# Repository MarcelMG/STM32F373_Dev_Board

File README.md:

# STM32F373_Dev_Board
a development board for the STM32F373 microcontroller with USB and separate analog power supply

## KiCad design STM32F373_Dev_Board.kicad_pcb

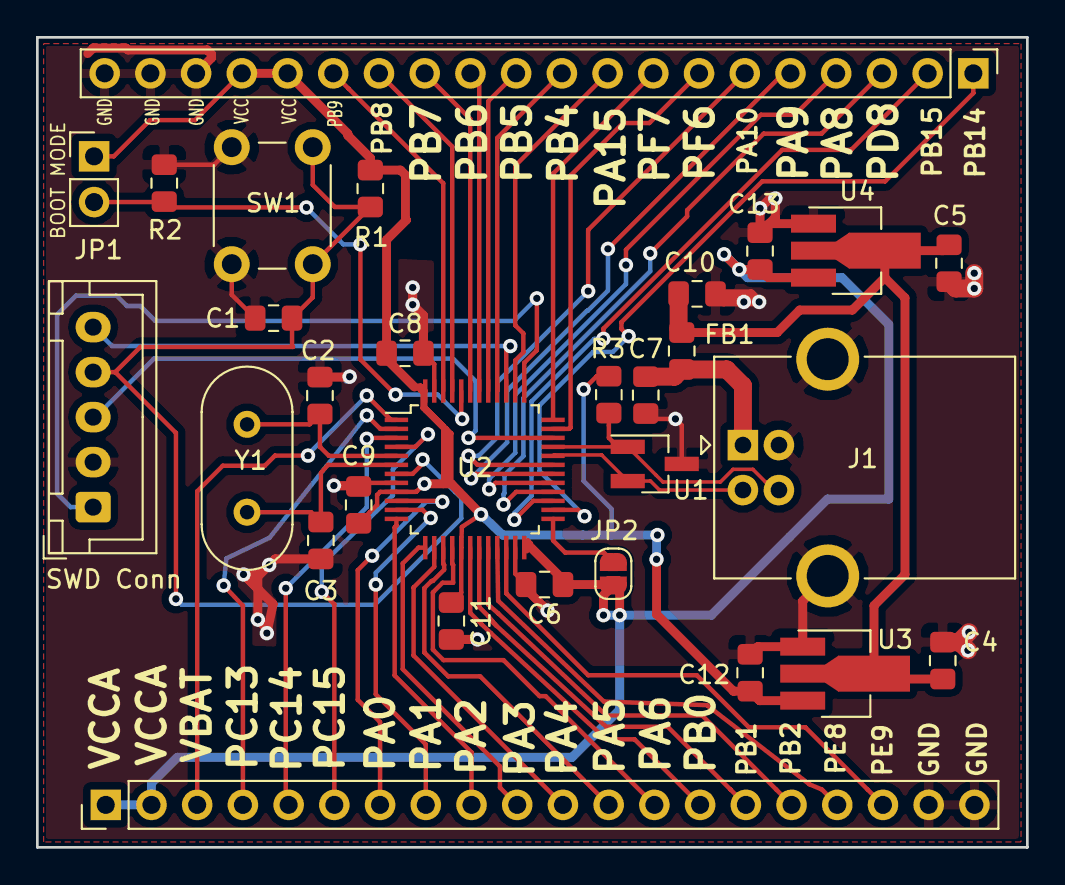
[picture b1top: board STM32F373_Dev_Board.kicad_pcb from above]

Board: 2 copper layers, 55.0 x 45.0 mm, 29 parts (0 on the bottom side), 46 nets.

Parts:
C1, C10: 100n; C_0805_2012Metric_Pad1.15x1.40mm_HandSolder
C2, C3: 27pF; C_0805_2012Metric_Pad1.15x1.40mm_HandSolder
C4, C5: 4.7µ; C_0805_2012Metric_Pad1.15x1.40mm_HandSolder
C6, C7, C8, C9, C11: 10n; C_0805_2012Metric_Pad1.15x1.40mm_HandSolder
C12, C13: 1µ; C_0805_2012Metric_Pad1.15x1.40mm_HandSolder
FB1: BLM21BB; L_0805_2012Metric_Pad1.15x1.40mm_HandSolder
J1: USB_B_female; USB_B_OST_USB-B1HSxx_Horizontal
J3, J4: Conn_01x20; PinHeader_1x20_P2.54mm_Vertical
JP1: Jumper; PinHeader_1x02_P2.54mm_Vertical
JP2: Jumper; SolderJumper-2_P1.3mm_Open_RoundedPad1.0x1.5mm
R1, R2: 10k; R_0805_2012Metric_Pad1.15x1.40mm_HandSolder
R3: 1.5k; R_0805_2012Metric_Pad1.15x1.40mm_HandSolder
SW1: SW_Push; SW_PUSH_6mm_H5mm
SWD Conn: SWD ST-Link Connector; JST_XH_B05B-XH-A_1x05_P2.50mm_Vertical
U1: TPD2E009; SOT-23_Handsoldering
U2: STM32F373CCTx; LQFP-48_7x7mm_P0.5mm
U3, U4: AP7215; SOT-89-3_Handsoldering
Y1: 8 MHz; Crystal_HC49-U_Vertical

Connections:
+3.3VA: C6.1, C13.1, J3.1, J3.2, JP2.2, U2.24, U4.3
+3V3: C8.1, C9.1, C11.1, C12.1, J4.16, J4.17, JP1.1, R1.2, R3.1, U2.9, U2.17, U2.48, U3.3
+5V: C4.1, C5.1, C10.2, FB1.1, U3.2, U4.2
BOOT0: JP1.2, R2.2, U2.44
GND: C1.1, C2.2, C3.2, C4.2, C5.2, C6.2, C7.1, C8.2, C9.2, C10.1, C11.2, C12.2, C13.2, J1.4, J1.5, J3.19, J3.20, J4.18, J4.19, J4.20, R2.1, SW1.1, SWD Conn.2, U1.3, U2.8, U2.23, U2.47, U3.1, U4.1
unnamed: C2.1, U2.5, Y1.1
unnamed: C3.1, U2.6, Y1.2
unnamed: J3.7, U2.10
unnamed: J3.8, U2.11
unnamed: J3.9, U2.12
unnamed: J3.10, U2.13
unnamed: J3.11, U2.14
unnamed: J3.12, U2.15
unnamed: J3.13, U2.16
unnamed: J4.4, U2.29
unnamed: J4.5, U2.30
unnamed: J4.6, U2.31
unnamed: J4.9, U2.38
unnamed: J4.10, U2.40
unnamed: J4.11, U2.41
unnamed: J4.12, U2.42
unnamed: J4.13, U2.43
unnamed: J4.14, U2.45
unnamed: J4.15, U2.46
unnamed: JP2.1, U2.25
PB0: J3.14, U2.18
PB1: J3.15, U2.19
PB2: J3.16, U2.20
PB14: J4.1, U2.26
PB15: J4.2, U2.27
PC13: J3.4, U2.2
PC14: J3.5, U2.3
PC15: J3.6, U2.4
PD8: J4.3, U2.28
PE8: J3.17, U2.21
PE9: J3.18, U2.22
PF6: J4.7, U2.35
PF7: J4.8, U2.36
RESET: C1.2, R1.1, SW1.2, SWD Conn.4, U2.7
SWDCLK: SWD Conn.1, U2.37
SWDIO: SWD Conn.3, U2.34
SWO: SWD Conn.5, U2.39
USB_D+: J1.3, R3.2, U1.1, U2.33
USB_D-: J1.2, U1.2, U2.32
USB_VBUS: C7.2, FB1.2, J1.1
VBAT: J3.3, U2.1

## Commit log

2020-01-27 removed unnecessary files
2020-01-27 renamed file to specify distributor

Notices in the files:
STM32F373_Dev_Board.kicad_pcb:
(c) 2019 by MarcelMG
